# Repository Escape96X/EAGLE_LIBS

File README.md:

# EAGLE_STUFF
My libraries and boards made by me.
You can use it whatever you want.

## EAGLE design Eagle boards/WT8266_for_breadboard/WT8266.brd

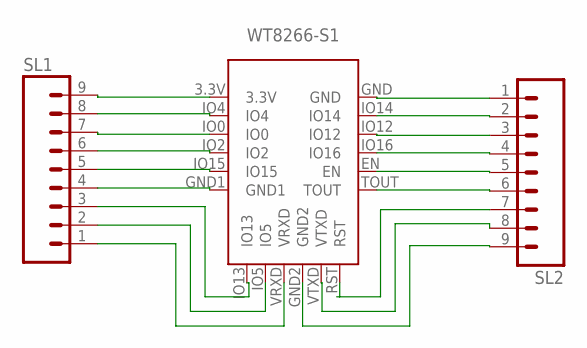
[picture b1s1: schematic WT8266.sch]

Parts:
SL1, SL2: MA09; 09PA
U$1: WT8266-S1

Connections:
unnamed: SL2.1, U$1.GND
unnamed: SL2.2, U$1.IO14
unnamed: SL2.3, U$1.IO12
unnamed: SL2.4, U$1.IO16
unnamed: SL2.5, U$1.EN
unnamed: SL2.6, U$1.TOUT
unnamed: SL2.7, U$1.RST
unnamed: SL2.8, U$1.VTXD
unnamed: SL2.9, U$1.GND2
unnamed: SL1.9, U$1.3.3V
unnamed: SL1.8, U$1.IO4
unnamed: SL1.7, U$1.IO0
unnamed: SL1.6, U$1.IO2
unnamed: SL1.5, U$1.IO15
unnamed: SL1.4, U$1.GND1
unnamed: SL1.3, U$1.IO13
unnamed: SL1.2, U$1.IO5
unnamed: SL1.1, U$1.VRXD

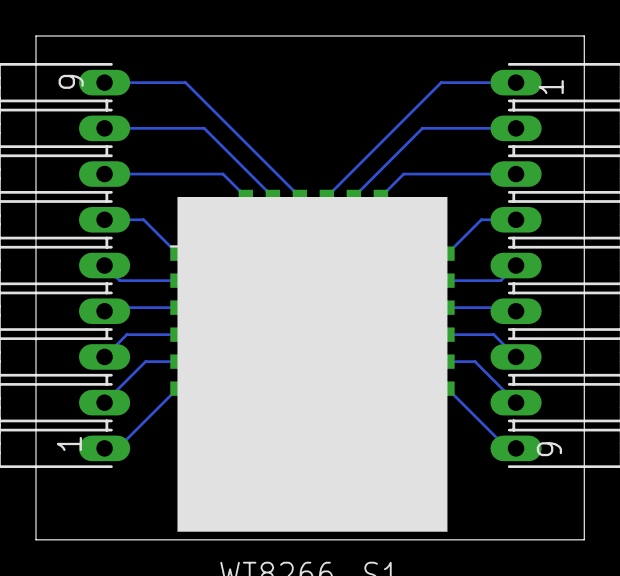
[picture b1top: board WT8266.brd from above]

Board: 2 copper layers, 30.5 x 28.0 mm, 3 parts (0 on the bottom side), 18 nets.

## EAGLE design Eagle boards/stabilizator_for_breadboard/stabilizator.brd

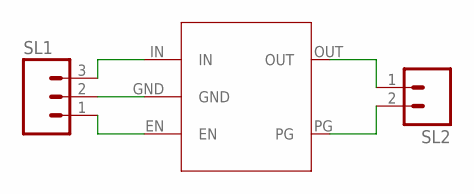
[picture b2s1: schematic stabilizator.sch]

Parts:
SL1: MA03; 03P
SL2: MA02; 02PA
U$1: LDLN030

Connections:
unnamed: SL1.3, U$1.IN
unnamed: SL1.2, U$1.GND
unnamed: SL1.1, U$1.EN
unnamed: SL2.1, U$1.OUT
unnamed: SL2.2, U$1.PG

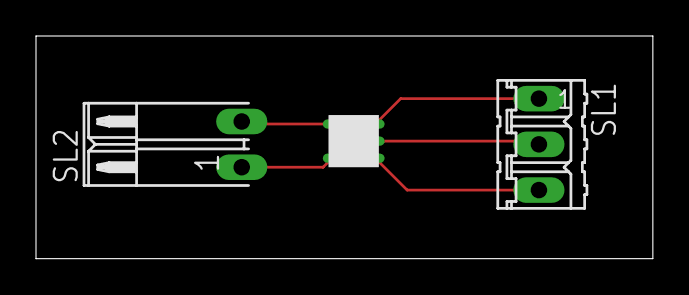
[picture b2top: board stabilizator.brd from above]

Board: 2 copper layers, 34.3 x 12.4 mm, 3 parts (0 on the bottom side), 5 nets.

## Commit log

2021-02-20 My eagle
